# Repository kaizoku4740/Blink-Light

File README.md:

# Blink-Light
A 555 LED chaser board project in the shape of a heart made to learn about electronics, schematic design and PCB layout in KiCad
The board lights up 10 LEDs in a sequence to create a rotating pattern that can be adjused with a potentiometer

WHy this was made
I created this product to introduce myself to the world of electronics, and the design was originally intended for mothers day but i forgot that already pased, and with fathers day approaching this will work for that. I positioned the leds along the perimeter of the heart as i thought that would look visually appealing.

| Item | Quantity |
|------|----------|
| NE555 Timer IC | 1 |
| CD4017 Counter IC | 1 |
| LEDs | 10 |
| 1000 ohm Resistor | 1 |
| 470 ohn Resistor | 1 |
| Potentiometer | 1 |
| 1 uF Capacitor | 1 |
| 0.01 uF Capacitor | 1 |
| 2-Pin Header | 1 |
| 1-Pin Header | 1 |

The cost for each part individually isnt known as hack club gives it in a combined kit, but that kit costs $10

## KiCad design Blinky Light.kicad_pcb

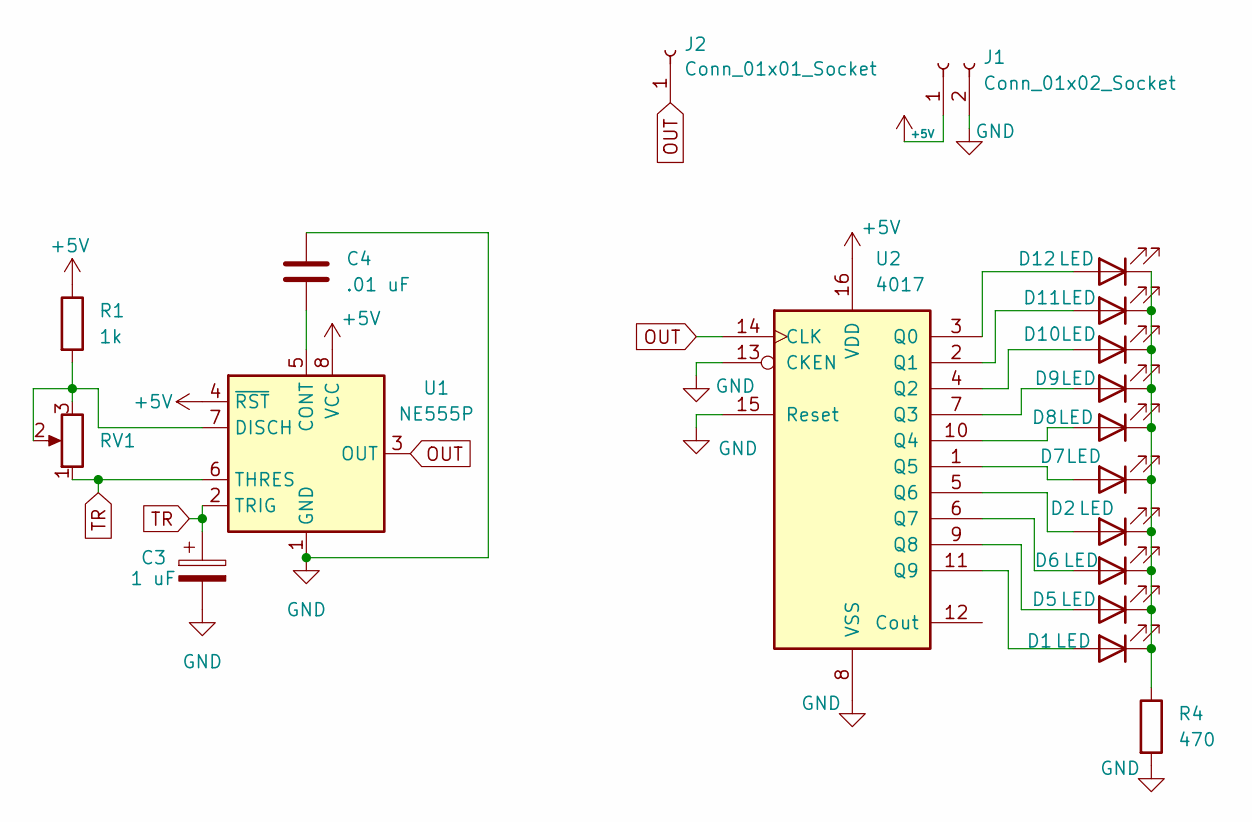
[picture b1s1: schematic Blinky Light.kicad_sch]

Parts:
C3: 1 uF; CP_Radial_D5.0mm_P2.00mm
C4: .01 uF; C_Disc_D7.5mm_W2.5mm_P5.00mm
D1, D2, D5, D6, D7, D8, D9, D10, D11, D12: LED; LED_D3.0mm
J1: Conn_01x02_Socket; PinHeader_1x02_P2.54mm_Vertical
J2: Conn_01x01_Socket; PinHeader_1x01_P2.54mm_Vertical
R1: 1k; R_Axial_DIN0207_L6.3mm_D2.5mm_P7.62mm_Horizontal
R4: 470; R_Axial_DIN0207_L6.3mm_D2.5mm_P7.62mm_Horizontal
RV1: R_Potentiometer; Potentiometer_Vishay_T93YA_Vertical
U1: NE555P; DIP-8_W7.62mm
U2: 4017; N16

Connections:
+5V: J1.1, R1.1, U1.4 (~RST), U1.8 (VCC), U2.16 (VDD)
GND: C3.2, C4.1, J1.2, R4.2, U1.1 (GND), U2.8 (VSS), U2.13 (CKEN), U2.15 (Reset)
unnamed: D1.2 (A), U2.11 (Q9)
unnamed: D1.1 (K), D2.1 (K), D5.1 (K), D6.1 (K), D7.1 (K), D8.1 (K), D9.1 (K), D10.1 (K), D11.1 (K), D12.1 (K), R4.1
unnamed: D2.2 (A), U2.5 (Q6)
unnamed: D5.2 (A), U2.9 (Q8)
unnamed: D6.2 (A), U2.6 (Q7)
unnamed: D7.2 (A), U2.1 (Q5)
unnamed: D8.2 (A), U2.10 (Q4)
unnamed: D9.2 (A), U2.7 (Q3)
unnamed: D10.2 (A), U2.4 (Q2)
unnamed: D11.2 (A), U2.2 (Q1)
unnamed: D12.2 (A), U2.3 (Q0)
unnamed: C4.2, U1.5 (CONT)
unnamed: R1.2, RV1.2, RV1.3, U1.7 (DISCH)
OUT: J2.1 (Pin_1_1), U1.3 (OUT), U2.14 (CLK)
TR: C3.1, RV1.1, U1.2 (TRIG), U1.6 (THRES)

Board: 2 copper layers, 19 parts (0 on the bottom side), 17 nets, no tracks yet.

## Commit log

2026-06-03 Update README with parts list and pricing
    Added a parts list and cost information to the README.
